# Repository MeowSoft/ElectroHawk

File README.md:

# ElectroHawk
ElectroHawk. Nuff said.

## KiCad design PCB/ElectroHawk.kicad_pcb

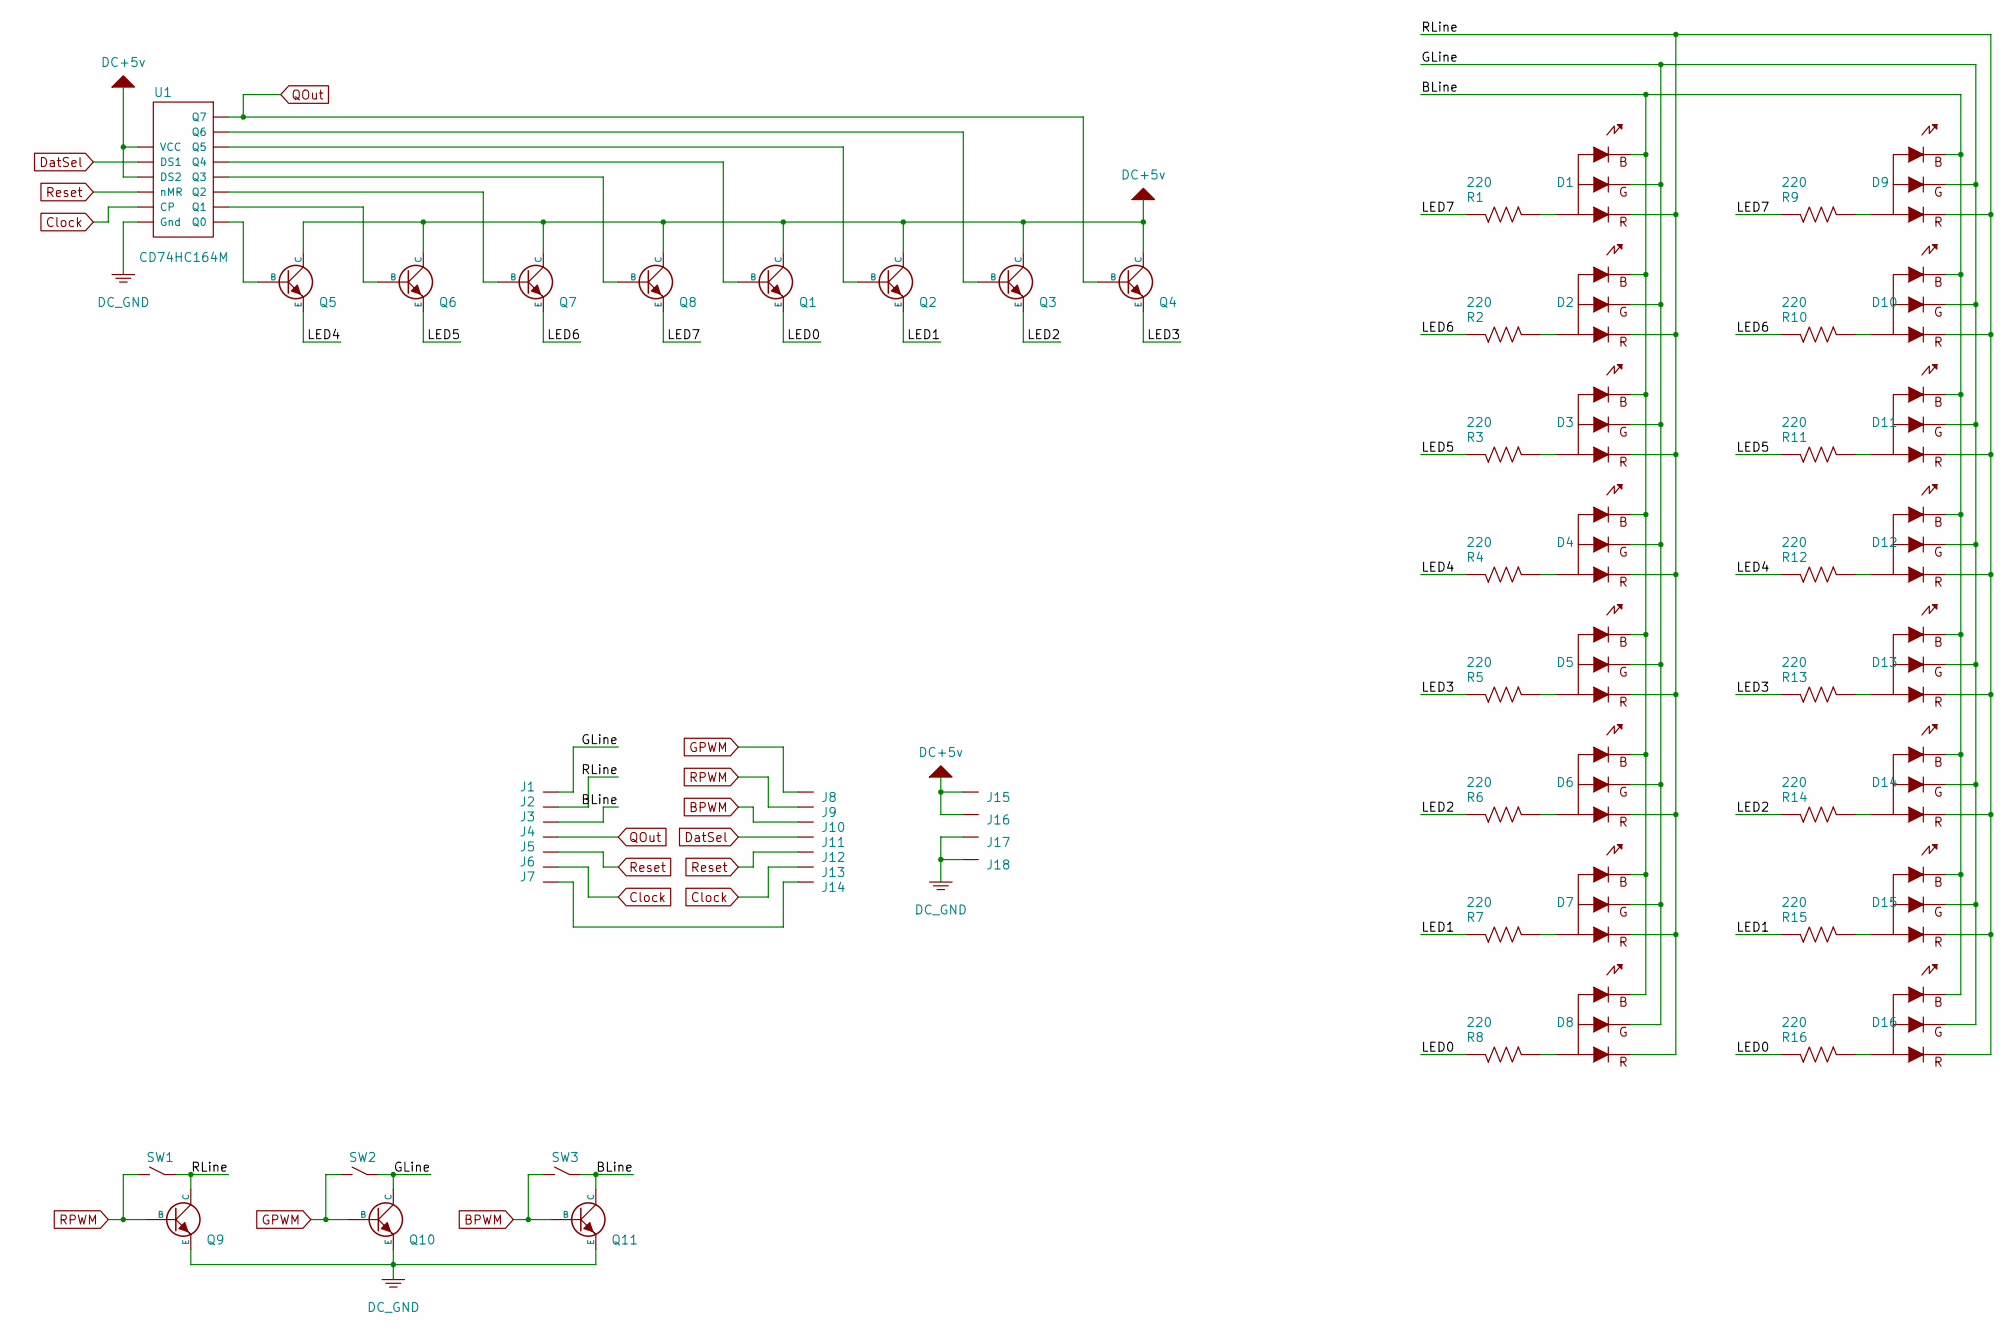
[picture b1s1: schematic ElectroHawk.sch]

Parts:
D1, D2, D3, D4, D5, D6, D7, D8, D9, D10, D11, D12, D13, D14, D15, D16: Cree_CLV1L-FKB-CHMMQEHBB7673673; PLCC-4; Mfr PN CLV1L-FKB-CHMMQEHBB7673673
J1, J2, J3, J4, J5, J6, J7, J8, J9, J10, J11, J12, J13, J14, J15, J16, J17, J18: Prototyping_Pad_01
Q1, Q2, Q3, Q4, Q5, Q6, Q7, Q8, Q9, Q10, Q11: Diodes-Inc_MMBT3904-7-F; SOT-23-3; Mfr PN MMBT3904-7-F
R1, R2, R3, R4, R5, R6, R7, R8, R9, R10, R11, R12, R13, R14, R15, R16: 00000220000_220_ERJ-6GEYJ221V; 0805; Tolerance 5%; Mfr PN ERJ-6GEYJ221V
SW1, SW2, SW3: Solder_Jumper_1Way; Solder_Jumper_1Way_Small; Mfr PN NA
U1: Texas-Instruments_CD74HC164M; SOIC-14; Mfr PN CD74HC164M

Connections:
+5V: J15.1, J16.1, Q1.3 (C), Q2.3 (C), Q3.3 (C), Q4.3 (C), Q5.3 (C), Q6.3 (C), Q7.3 (C), Q8.3 (C), U1.2 (DS2), U1.14 (VCC)
/BLine: D1.4 (B), D2.4 (B), D3.4 (B), D4.4 (B), D5.4 (B), D6.4 (B), D7.4 (B), D8.4 (B), D9.4 (B), D10.4 (B), D11.4 (B), D12.4 (B), D13.4 (B), D14.4 (B), D15.4 (B), D16.4 (B), J3.1, Q11.3 (C), SW3.2
/GLine: D1.3 (G), D2.3 (G), D3.3 (G), D4.3 (G), D5.3 (G), D6.3 (G), D7.3 (G), D8.3 (G), D9.3 (G), D10.3 (G), D11.3 (G), D12.3 (G), D13.3 (G), D14.3 (G), D15.3 (G), D16.3 (G), J1.1, Q10.3 (C), SW2.2
/LED0: Q1.2 (E), R8.1, R16.1
/LED1: Q2.2 (E), R7.1, R15.1
/LED2: Q3.2 (E), R6.1, R14.1
/LED3: Q4.2 (E), R5.1, R13.1
/LED4: Q5.2 (E), R4.1, R12.1
/LED5: Q6.2 (E), R3.1, R11.1
/LED6: Q7.2 (E), R2.1, R10.1
/LED7: Q8.2 (E), R1.1, R9.1
/RLine: D1.2 (R), D2.2 (R), D3.2 (R), D4.2 (R), D5.2 (R), D6.2 (R), D7.2 (R), D8.2 (R), D9.2 (R), D10.2 (R), D11.2 (R), D12.2 (R), D13.2 (R), D14.2 (R), D15.2 (R), D16.2 (R), J2.1, Q9.3 (C), SW1.2
BPWM: J10.1, Q11.1 (B), SW3.1
Clock: J6.1, J13.1, U1.8 (CP)
DC_GND: J17.1, J18.1, Q9.2 (E), Q10.2 (E), Q11.2 (E), U1.7 (Gnd)
DatSel: J11.1, U1.1 (DS1)
GPWM: J8.1, Q10.1 (B), SW2.1
unnamed: D1.1 (A), R1.2
unnamed: D2.1 (A), R2.2
unnamed: D3.1 (A), R3.2
unnamed: D4.1 (A), R4.2
unnamed: D5.1 (A), R5.2
unnamed: D6.1 (A), R6.2
unnamed: D7.1 (A), R7.2
unnamed: D8.1 (A), R8.2
unnamed: D9.1 (A), R9.2
unnamed: D10.1 (A), R10.2
unnamed: D11.1 (A), R11.2
unnamed: D12.1 (A), R12.2
unnamed: D13.1 (A), R13.2
unnamed: D14.1 (A), R14.2
unnamed: D15.1 (A), R15.2
unnamed: D16.1 (A), R16.2
unnamed: J7.1, J14.1
unnamed: Q1.1 (B), U1.10 (Q4)
unnamed: Q2.1 (B), U1.11 (Q5)
unnamed: Q3.1 (B), U1.12 (Q6)
unnamed: Q5.1 (B), U1.3 (Q0)
unnamed: Q6.1 (B), U1.4 (Q1)
unnamed: Q7.1 (B), U1.5 (Q2)
unnamed: Q8.1 (B), U1.6 (Q3)
QOut: J4.1, Q4.1 (B), U1.13 (Q7)
RPWM: J9.1, Q9.1 (B), SW1.1
Reset: J5.1, J12.1, U1.9 (nMR)

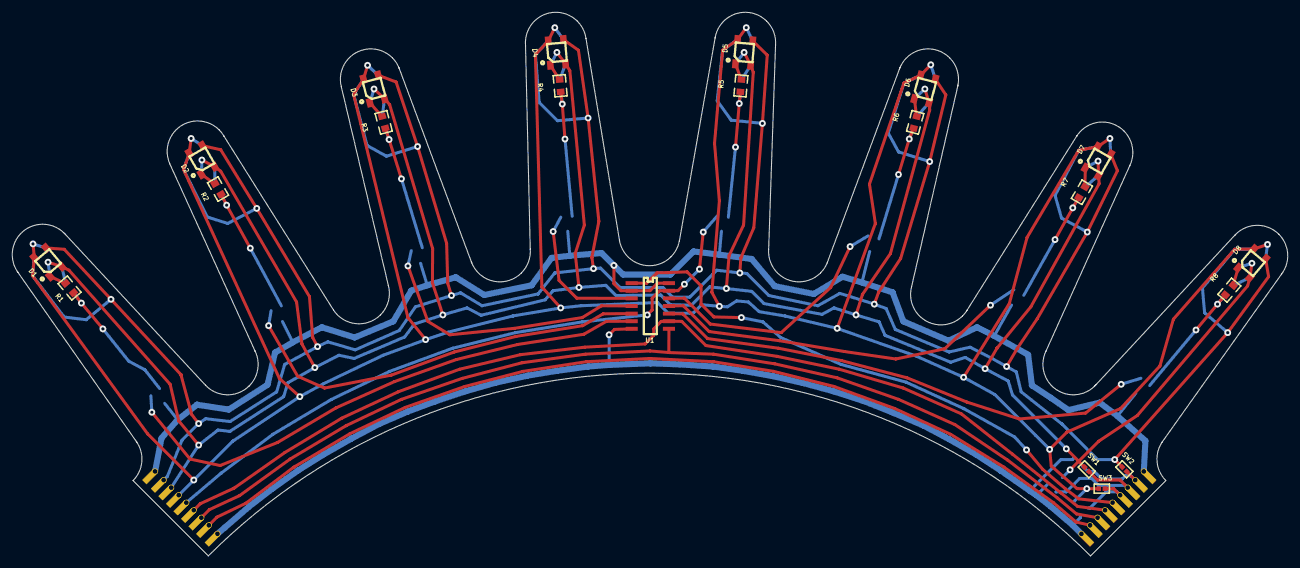
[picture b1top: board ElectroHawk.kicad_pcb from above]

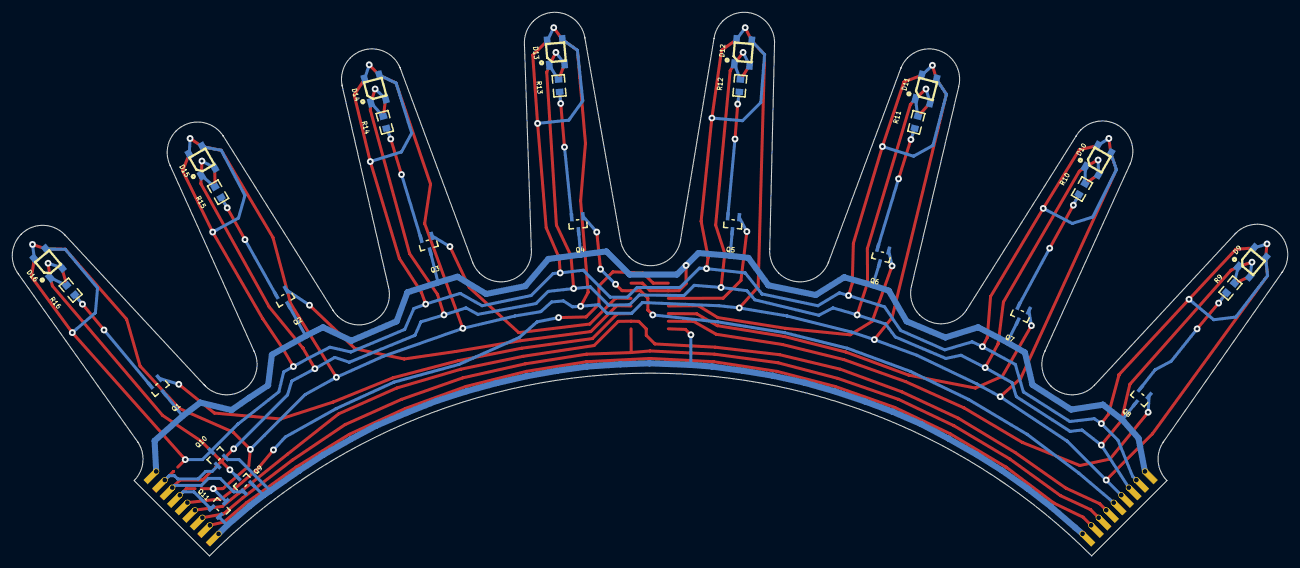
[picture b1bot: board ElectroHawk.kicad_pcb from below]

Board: 2 copper layers, 212.9 x 90.8 mm, 65 parts (27 on the bottom side), 44 nets.

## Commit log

2015-11-13 Adding KiCad project files.
2015-11-13 Adding ElectroHawk.ino.
